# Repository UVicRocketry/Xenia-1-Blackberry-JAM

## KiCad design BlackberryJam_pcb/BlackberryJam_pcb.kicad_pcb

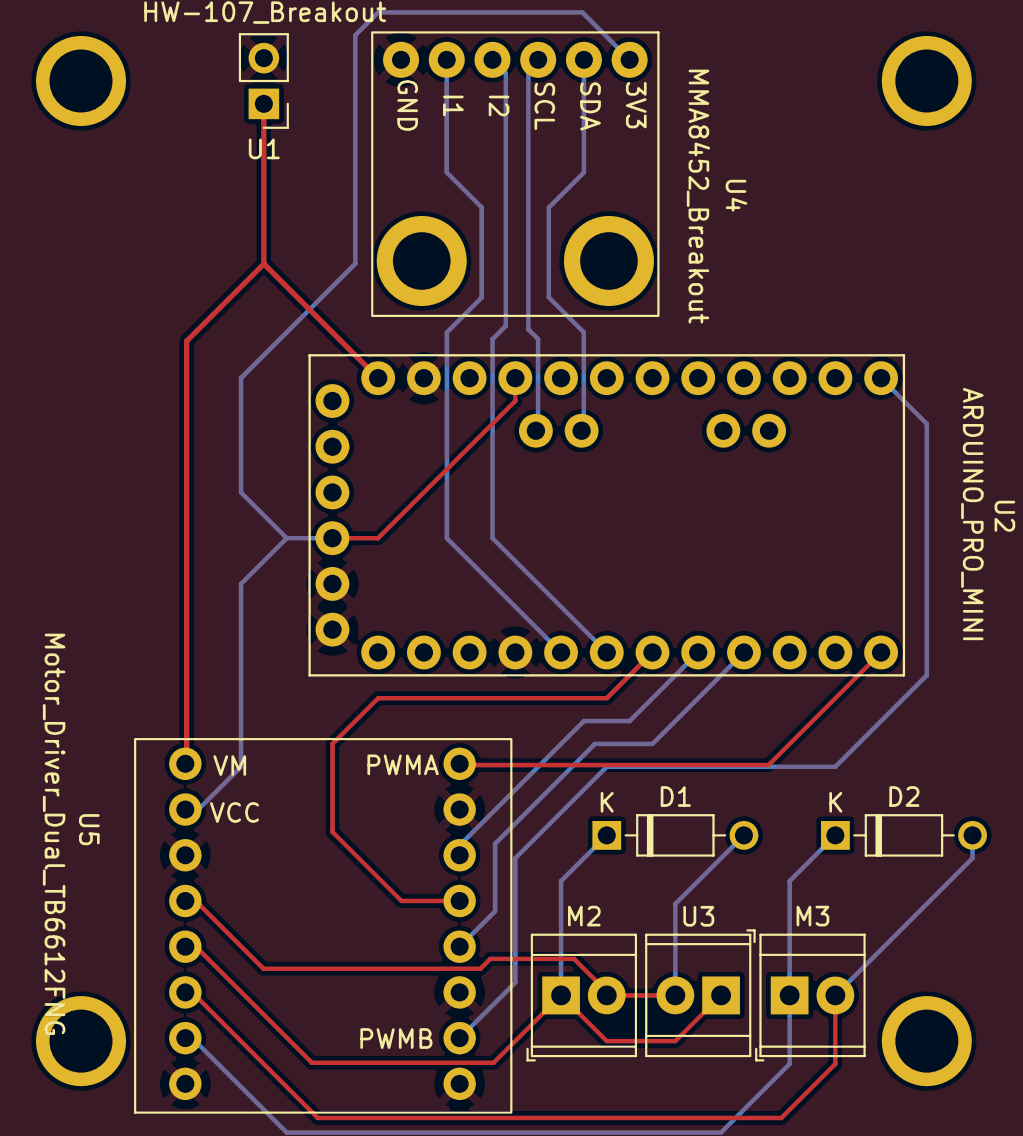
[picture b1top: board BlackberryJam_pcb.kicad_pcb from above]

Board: 2 copper layers, 10 parts (1 on the bottom side), 16 nets.

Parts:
D1, D2: 1N4148; D_DO-35_SOD27_P7.62mm_Horizontal
M2: PUMP2; TerminalBlock_TE_282834-2_1x02_P2.54mm_Horizontal
M3: CONTROL GROUP MOTOR; TerminalBlock_TE_282834-2_1x02_P2.54mm_Horizontal
U1: HW-107_Breakout; PinHeader_1x02_P2.54mm_Vertical
U2: ARDUINO_PRO_MINI
U3: Slip_Ring; TerminalBlock_TE_282834-2_1x02_P2.54mm_Horizontal
U4: MMA8452_Breakout; MMA8452Q_Breakout
U5: Motor_Driver_Dual_TB6612FNG; Dual_Motor_Driver
UVR 2022 XENIA-1 : LOGO

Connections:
A4: U2.JP2_1 (A4), U4.2 (SDA)
A5: U2.JP2_2 (A5), U4.3 (SCL)
D2 (INT0): U2.JP7_8 (D2), U4.5 (INT1)
D3 (INT1): U2.JP7_7 (D3), U4.4 (INT2)
D4: U2.JP7_6 (D4), U5.13 (STBY)
D5: U2.JP7_5 (D5), U5.14 (AI1)
D6: U2.JP7_4 (D6), U5.12 (BI1)
D9 (PWM): U2.JP7_1 (D9), U5.16 (PWMA)
D10 (PWM): U2.JP6_12 (D10), U5.10 (PWMB)
GND: U1.6 (OUT-), U2.JP1_5 (GND), U2.JP1_6 (GND), U2.JP6_2 (GND_1), U2.JP7_9 (GND_2), U4.6 (GND), U5.3 (GND), U5.8 (GND), U5.9 (GND), U5.11 (BI2), U5.15 (AI2)
unnamed: D1.1 (K), M2.1 (+), U3.1 (+IN), U5.5 (A02)
unnamed: D1.2 (A), M2.2 (-), U3.2 (-IN), U5.4 (A01)
unnamed: D2.1 (K), M3.1 (+), U5.7 (B01)
unnamed: D2.2 (A), M3.2 (-), U5.6 (B02)
RAW (V_IN): U1.5 (OUT+), U2.JP6_1 (RAW), U5.1 (VM)
VCC (3.3V): U2.JP1_4 (VCC), U2.JP6_4 (VCC_1), U4.1 (3.3V), U5.2 (VCC)
